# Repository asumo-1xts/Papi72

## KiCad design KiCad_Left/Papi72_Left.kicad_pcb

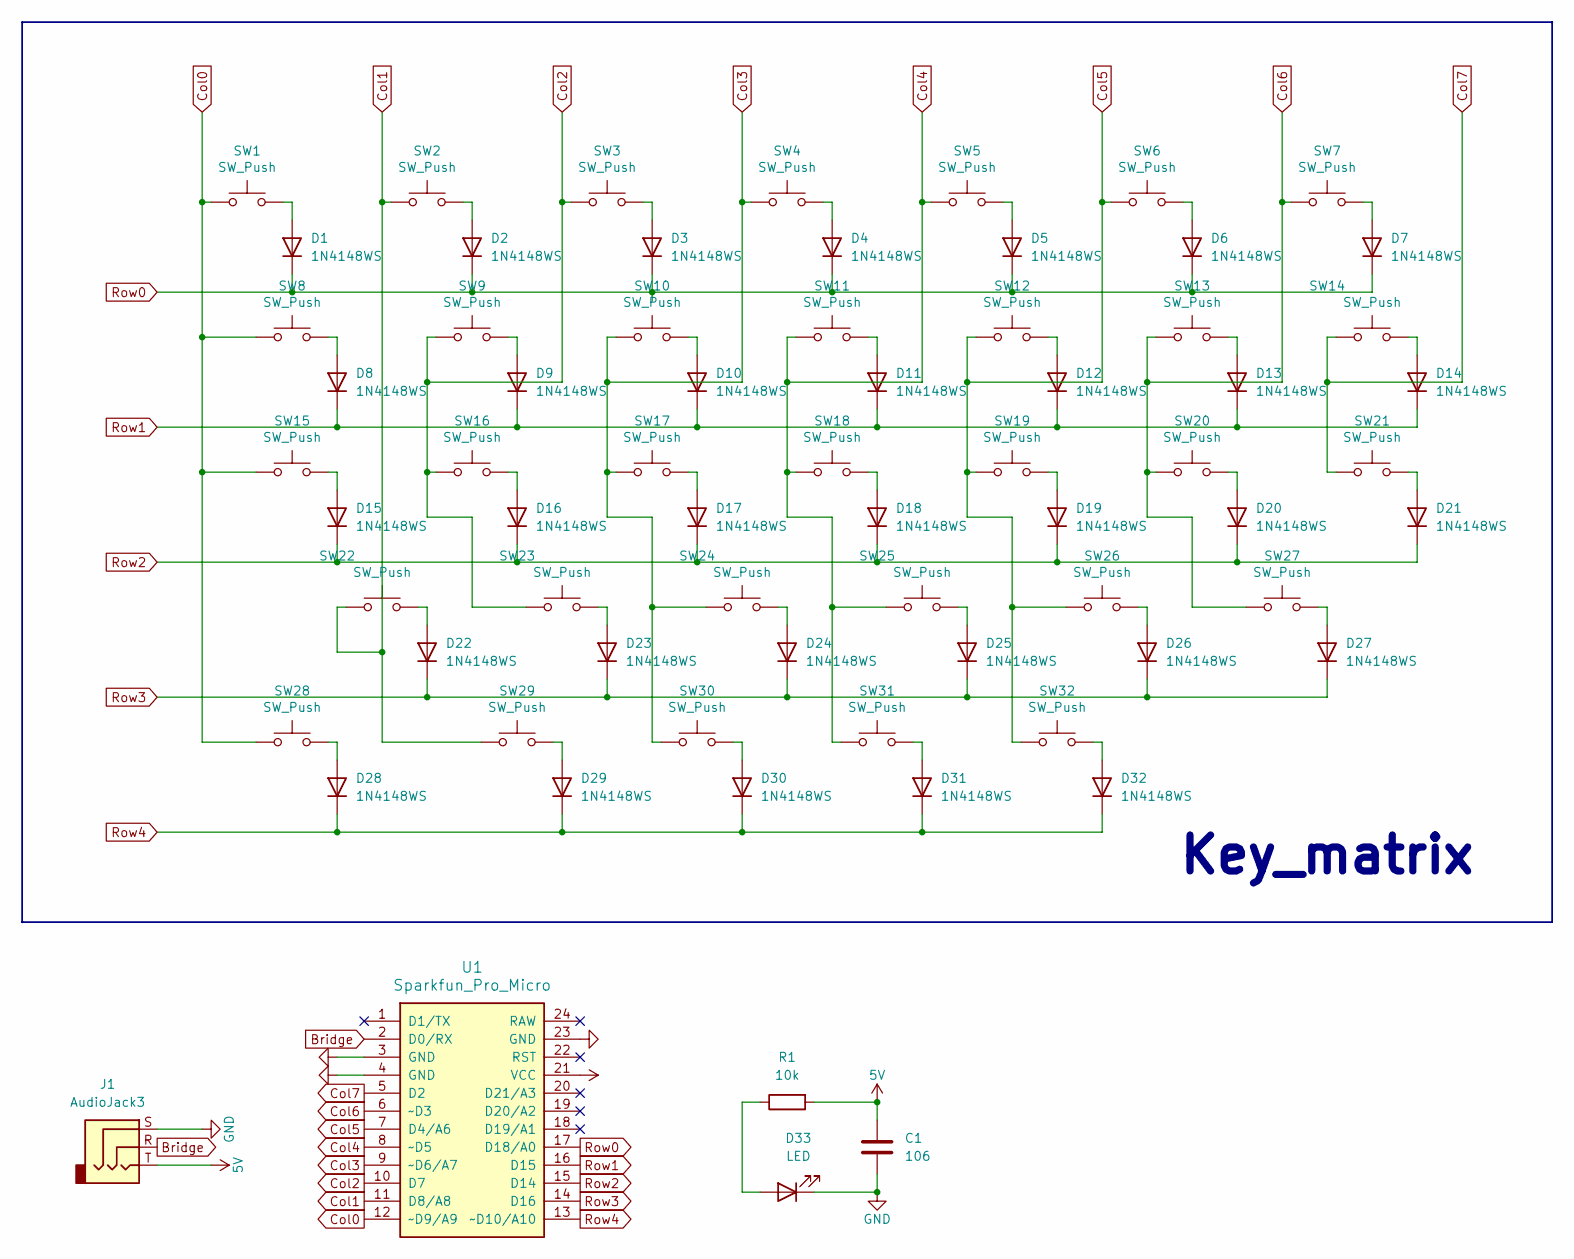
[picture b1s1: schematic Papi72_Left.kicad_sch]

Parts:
C1: 106; C_1206_3216Metric
D1, D2, D3, D4, D5, D6, D7, D8, D9, D10, D11, D12, D13, D14, D15, D16, D17, D18, D19, D20, D21, D22, D23, D24, D25, D26, D27, D28, D29, D30, D31, D32: 1N4148WS; D_SOD-323
D33: LED; LED_D3.0mm_Clear
J1: AudioJack3; Jack_3.5mm_CUI_SJ1-3513N_Horizontal
R1: 10k; R_0805_2012Metric
SW1, SW2, SW3, SW4, SW5, SW6, SW7, SW9, SW10, SW11, SW12, SW13, SW14, SW16, SW17, SW18, SW19, SW20, SW21, SW23, SW24, SW25, SW26, SW27: SW_Push; SW_Kailh_Choc_V1V2_1.00u
SW8: SW_Push; SW_Kailh_Choc_V1V2_1.50u
SW15, SW32: SW_Push; SW_Kailh_Choc_V1V2_1.75u
SW22: SW_Push; SW_Kailh_Choc_V1V2_2.25u
SW28, SW29, SW30, SW31: SW_Push; SW_Kailh_Choc_V1V2_1.25u
U1: Sparkfun_Pro_Micro

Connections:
5V: C1.1, J1.T, R1.2, U1.21 (VCC)
Bridge: J1.R, U1.2 (D0/RX)
Col0: SW1.1, SW8.1, SW15.1, SW28.1, U1.12 (~D9/A9)
Col1: SW2.1, SW22.1, SW29.1, U1.11 (D8/A8)
Col2: SW3.1, SW9.1, SW16.1, SW23.1, U1.10 (D7)
Col3: SW4.1, SW10.1, SW17.1, SW24.1, SW30.1, U1.9 (~D6/A7)
Col4: SW5.1, SW11.1, SW18.1, SW25.1, SW31.1, U1.8 (~D5)
Col5: SW6.1, SW12.1, SW19.1, SW26.1, SW32.1, U1.7 (D4/A6)
Col6: SW7.1, SW13.1, SW20.1, SW27.1, U1.6 (~D3)
Col7: SW14.1, SW21.1, U1.5 (D2)
GND: C1.2, D33.1 (K), J1.S, U1.3 (GND), U1.4 (GND), U1.23 (GND); also elsewhere on the board
unnamed: D1.2 (A), SW1.2
unnamed: D2.2 (A), SW2.2
unnamed: D3.2 (A), SW3.2
unnamed: D4.2 (A), SW4.2
unnamed: D5.2 (A), SW5.2
unnamed: D6.2 (A), SW6.2
unnamed: D7.2 (A), SW7.2
unnamed: D8.2 (A), SW8.2
unnamed: D9.2 (A), SW9.2
unnamed: D10.2 (A), SW10.2
unnamed: D11.2 (A), SW11.2
unnamed: D12.2 (A), SW12.2
unnamed: D13.2 (A), SW13.2
unnamed: D14.2 (A), SW14.2
unnamed: D15.2 (A), SW15.2
unnamed: D16.2 (A), SW16.2
unnamed: D17.2 (A), SW17.2
unnamed: D18.2 (A), SW18.2
unnamed: D19.2 (A), SW19.2
unnamed: D20.2 (A), SW20.2
unnamed: D21.2 (A), SW21.2
unnamed: D22.2 (A), SW22.2
unnamed: D23.2 (A), SW23.2
unnamed: D24.2 (A), SW24.2
unnamed: D25.2 (A), SW25.2
unnamed: D26.2 (A), SW26.2
unnamed: D27.2 (A), SW27.2
unnamed: D28.2 (A), SW28.2
unnamed: D29.2 (A), SW29.2
unnamed: D30.2 (A), SW30.2
unnamed: D31.2 (A), SW31.2
unnamed: D32.2 (A), SW32.2
unnamed: D33.2 (A), R1.1
Row0: D1.1 (K), D2.1 (K), D3.1 (K), D4.1 (K), D5.1 (K), D6.1 (K), D7.1 (K), U1.17 (D18/A0)
Row1: D8.1 (K), D9.1 (K), D10.1 (K), D11.1 (K), D12.1 (K), D13.1 (K), D14.1 (K), U1.16 (D15)
Row2: D15.1 (K), D16.1 (K), D17.1 (K), D18.1 (K), D19.1 (K), D20.1 (K), D21.1 (K), U1.15 (D14)
Row3: D22.1 (K), D23.1 (K), D24.1 (K), D25.1 (K), D26.1 (K), D27.1 (K), U1.14 (D16)
Row4: D28.1 (K), D29.1 (K), D30.1 (K), D31.1 (K), D32.1 (K), U1.13 (~D10/A10)

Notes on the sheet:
Key_matrix

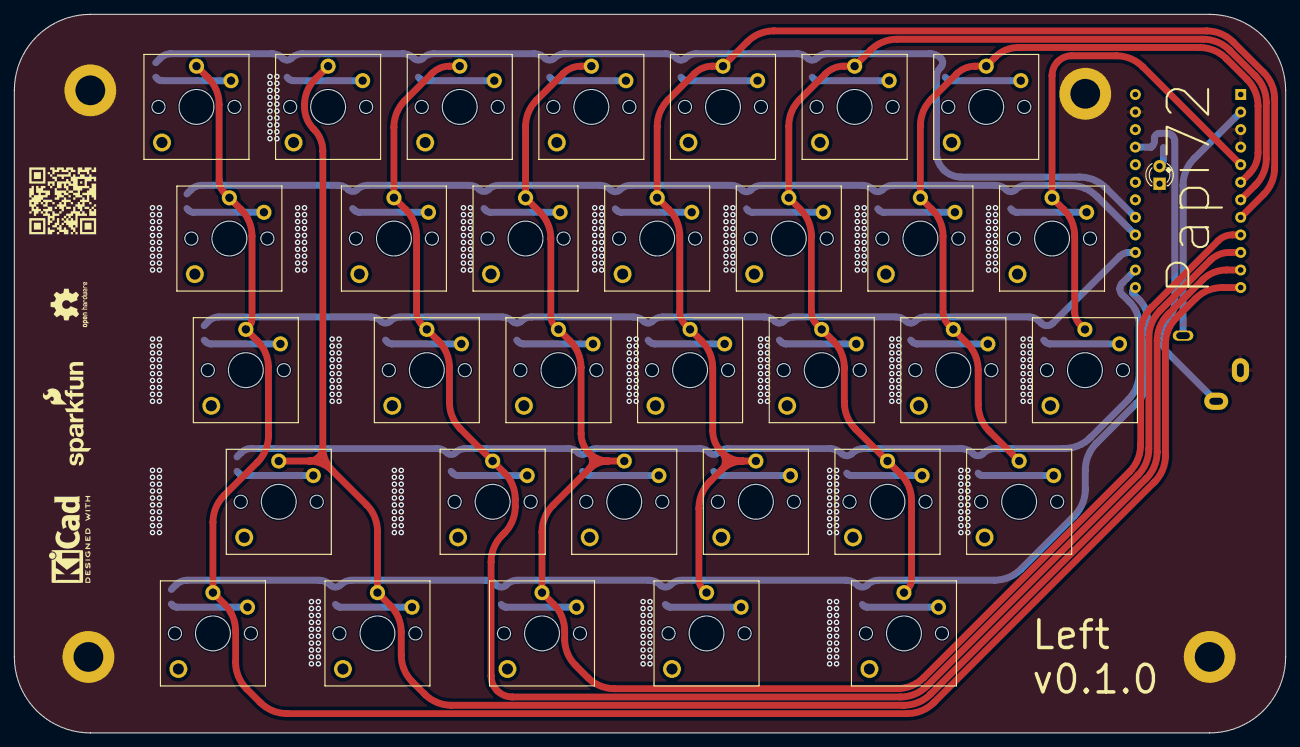
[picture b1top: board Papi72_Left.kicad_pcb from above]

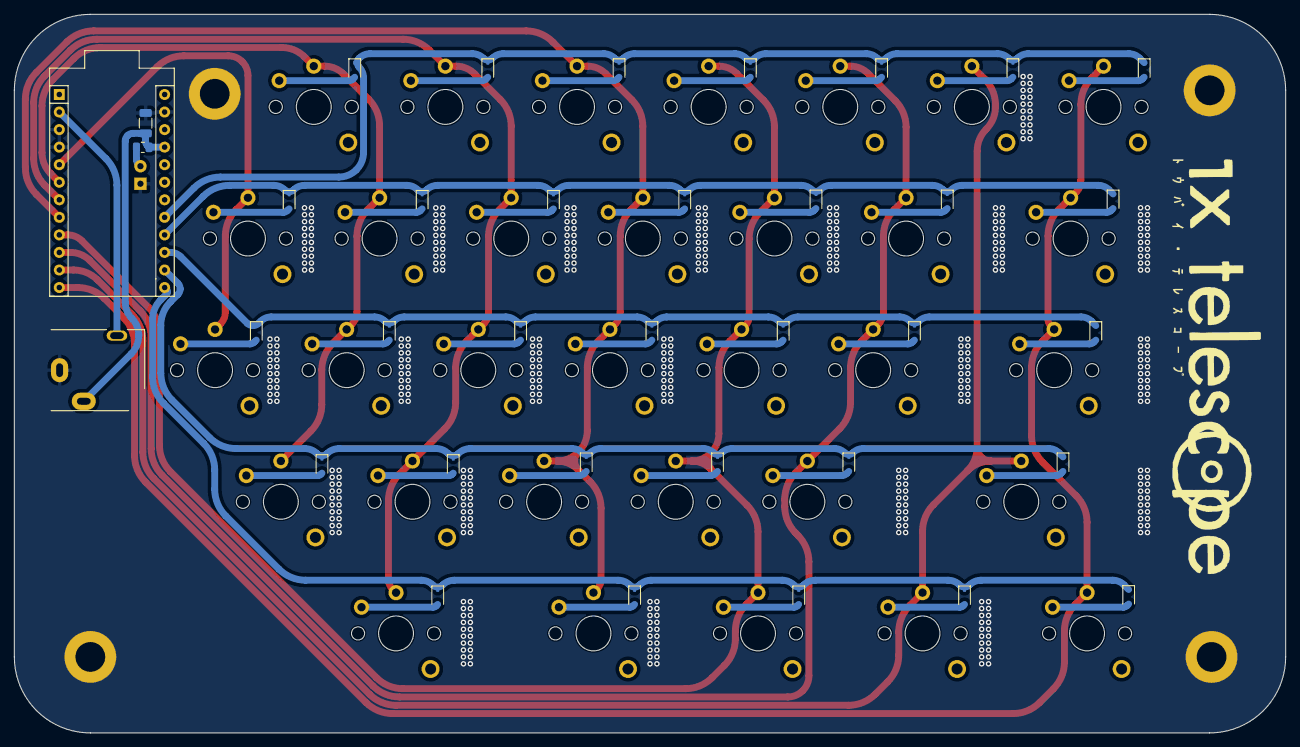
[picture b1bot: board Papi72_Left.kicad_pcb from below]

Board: 2 copper layers, 184.0 x 104.0 mm, 75 parts (37 on the bottom side), 49 nets.

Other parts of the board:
G5, G9: LOGO
G10: LOGO; SparkFun_Logo_15mm
G11: KiCad-Logo2_5mm_SilkScreen
G12: OSHW-Logo2_7.3x6mm_SilkScreen
H1: MountingHole_4.3mm_M4_DIN965_Pad

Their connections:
GND: H1.1; also elsewhere on the board

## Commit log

2025-11-24 delete: 不要なファイルを削除
2025-11-24 add: MITライセンスを追加
